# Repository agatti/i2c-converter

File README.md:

Quick and dirty attempt at a I2C&lt;&gt;USB converter board based on Silicon Labs' CP2112 I2C/SMBus bridge IC.

The main reason for coming up with this rather than use a ready made solution like an Arduino is to bypass UART-based communication to the I2C bus and talk to the I2C device using raw USB packets via LibUSB, and therefore avoiding to write an extra firmware for the Arduino (or any other MCU, really).  The CP2112 allows for control of 8 GPIO pins, which can be connected to a MCU if so needed too (the board has those pins exposed).

**Warning**: the board has not been tested yet (it's marked as v0.3 for a reason), use that at your own risk.

The board source files (everything in the "hardware" directory) are placed under the Creative Commons "ShareAlike 1.0 Generic" licence, whose text can be found here: https://creativecommons.org/licenses/sa/1.0/

The software part of the project has not been written yet, although it'll probably be released under the ZLib licence.

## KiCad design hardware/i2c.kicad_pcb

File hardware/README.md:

Quick and dirty version of a CP2112 I2C&lt;&gt;USB converter board, no real changes from the reference design in the component datasheet and layout is approximate at best...

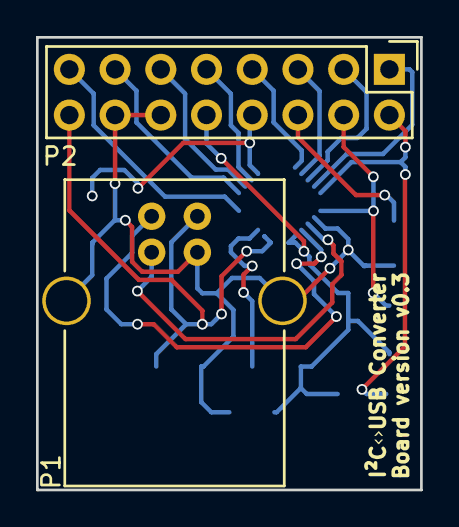
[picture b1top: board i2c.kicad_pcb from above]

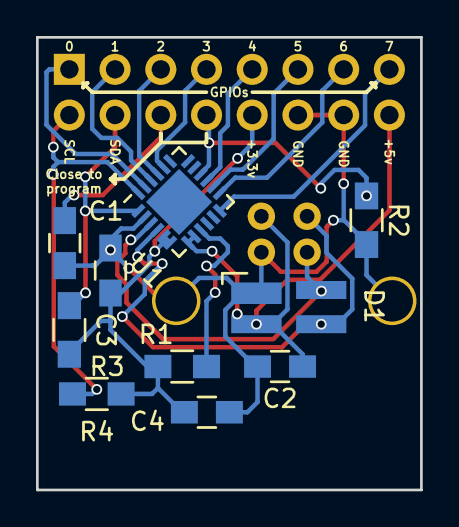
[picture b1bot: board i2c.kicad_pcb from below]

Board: 2 copper layers, 21.3 x 25.1 mm, 12 parts (10 on the bottom side), 18 nets.

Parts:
C1: 4.7µF; C_0805_HandSoldering
C2, C3: 1µF; C_0805_HandSoldering
C4: 0.1µF; C_0805_HandSoldering
D1: SP0503BAHTG; SOT-143_Handsoldering
P1: USB_B
P2: HEADER; Pin_Header_Straight_2x08
R1, R3, R4: 4.7kΩ; R_0805_HandSoldering
R2: 10kΩ; R_0805_HandSoldering
U1: CP2112; QFN-24-1EP_4x4mm_Pitch0.5mm

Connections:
/D+: D1.4, P1.3, U1.3
/D-: D1.3, P1.2, U1.4
/GPIO.0: P2.1, U1.23
/GPIO.1: P2.3, U1.22
/GPIO.2: P2.5, U1.21
/GPIO.3: P2.7, U1.20
/GPIO.4: P2.9, U1.15
/GPIO.5: P2.11, U1.14
/GPIO.6: P2.13, U1.13
/GPIO.7: P2.15, U1.12
/SCL: P2.2, R4.2, U1.24
/SDA: P2.4, R3.1, U1.1
/VPP: P2.8, R2.1, U1.16
GND: C1.1, C2.2, C3.2, C4.2, D1.1, P1.4, P1.5, P2.12, P2.14, R2.2, U1.2
unnamed: C1.2, P2.6
unnamed: R1.2, U1.9
VCC: C2.1, D1.2, P1.1, P2.16, U1.7, U1.8
VDD: C3.1, C4.1, P2.10, R1.1, R3.2, R4.1, U1.5, U1.6

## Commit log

2016-07-12 Initial commit.
2016-07-14 Expose more pins on the board.
2016-07-14 Move U1 passives closer to the IC.
2016-07-14 Widen GND/Vcc tracks.
2016-07-14 Remove stray component library.
2016-07-17 New form factor.
2016-07-17 Update readme version number.
2016-07-17 Add I2C pullup resistors.
2016-07-17 Cleanup schema and layout.
